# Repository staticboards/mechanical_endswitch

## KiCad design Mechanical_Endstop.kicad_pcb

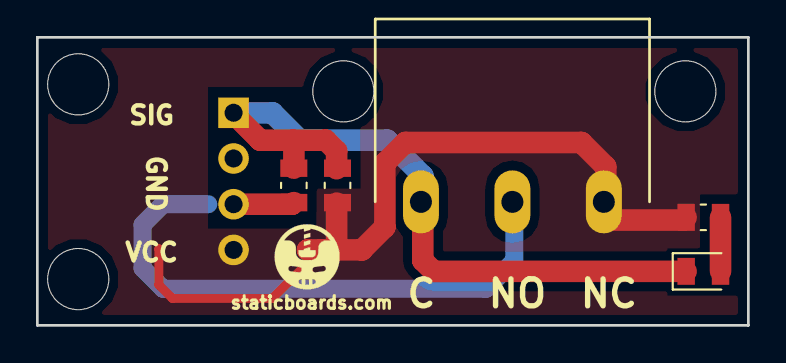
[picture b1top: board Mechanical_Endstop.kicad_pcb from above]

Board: 2 copper layers, 39.5 x 16.0 mm, 6 parts (0 on the bottom side), 4 nets.

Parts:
C1: 100nF; C_0805_2012Metric
D1: Detect; D_0805_2012Metric
J1: .; PinHeader_1x04_P2.54mm_Horizontal
R1: 1K; R_0805_2012Metric
R2: 10K; R_0805_2012Metric
SW1: StopSwitch

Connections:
/GND: C1.2, J1.2, J1.3, SW1.2
/SIG: C1.1, D1.1, J1.1, R2.2, SW1.1
/Vcc: J1.4, R1.1, R2.1, SW1.3
unnamed: D1.2, R1.2

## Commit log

2018-11-08 initial release
2018-11-08 images and licenses
